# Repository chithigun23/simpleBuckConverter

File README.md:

# simpleBuckConverter

The aim is to create a simple buck converter design that can be easily used in other projects. The rough guideline is 12V to 5V with 2A of peak load, but still efficient at minimal load.

I've added the following features:

* Low current efficiency with automatic PFM and PWM mode switching
* Reverse polarity protection, with low quiescent current draw
* Transient voltage suppression diodes on input

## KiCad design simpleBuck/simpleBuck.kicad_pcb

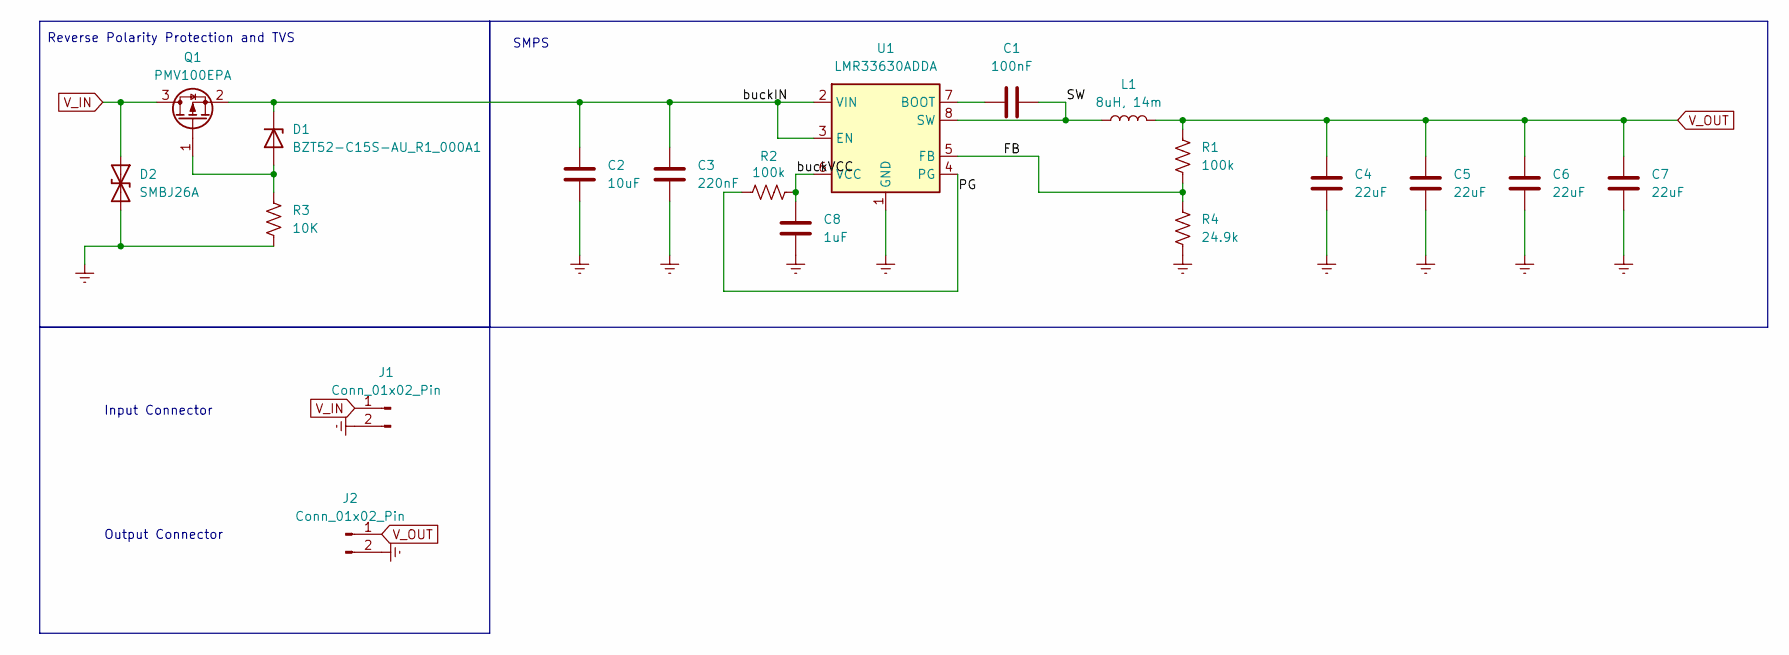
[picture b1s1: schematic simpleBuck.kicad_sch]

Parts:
C1: 100nF; C_0805_2012Metric_Pad1.18x1.45mm_HandSolder
C2: 10uF; C_0805_2012Metric_Pad1.18x1.45mm_HandSolder
C3: 220nF; C_0805_2012Metric_Pad1.18x1.45mm_HandSolder
C4, C5, C6, C7: 22uF; C_0805_2012Metric_Pad1.18x1.45mm_HandSolder
C8: 1uF; C_0805_2012Metric_Pad1.18x1.45mm_HandSolder
D1: BZT52-C15S-AU_R1_000A1; D_SOD-123
D2: SMBJ26A; C_0402_1005Metric_Pad0.74x0.62mm_HandSolder
J1, J2: Conn_01x02_Pin; PinHeader_1x02_P2.54mm_Vertical
L1: 8uH, 14m; L_TaiTech_TMPC1265_13.5x12.5mm
Q1: PMV100EPA; TSOT-23_HandSoldering
R1, R2: 100k; C_0805_2012Metric_Pad1.18x1.45mm_HandSolder
R3: 10K; C_0805_2012Metric_Pad1.18x1.45mm_HandSolder
R4: 24.9k; C_0805_2012Metric_Pad1.18x1.45mm_HandSolder
U1: LMR33630ADDA; Texas_HSOP-8-1EP_3.9x4.9mm_P1.27mm_ThermalVias

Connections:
/FB: R1.2, R4.1, U1.5 (FB)
/PG: R2.1, U1.4 (PG)
/SW: C1.2, L1.1, U1.8 (SW)
/buckIN: C2.1, C3.1, D1.1 (K), Q1.2 (S), U1.2 (VIN), U1.3 (EN)
/buckVCC: C8.1, R2.2, U1.6 (VCC)
GND: C2.2, C3.2, C4.2, C5.2, C6.2, C7.2, C8.2, D2.2 (A2), J1.2, J2.2, R3.2, R4.2, U1.1 (GND), U1.9 (GND)
unnamed: D1.2 (A), Q1.1 (G), R3.1
unnamed: C1.1, U1.7 (BOOT)
V_IN: D2.1 (A1), J1.1, Q1.3 (D)
V_OUT: C4.1, C5.1, C6.1, C7.1, J2.1, L1.2, R1.1

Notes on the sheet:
Reverse Polarity Protection and TVS
Output Connector
Input Connector
SMPS

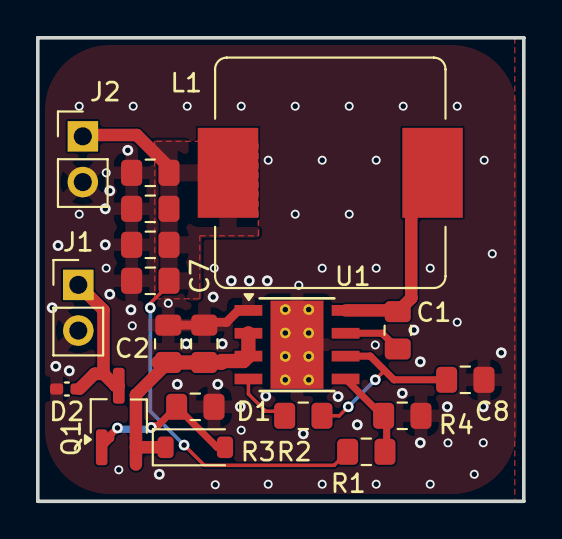
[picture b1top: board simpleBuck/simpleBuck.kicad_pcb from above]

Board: 2 copper layers, 27.0 x 25.8 mm, 19 parts (0 on the bottom side), 10 nets.

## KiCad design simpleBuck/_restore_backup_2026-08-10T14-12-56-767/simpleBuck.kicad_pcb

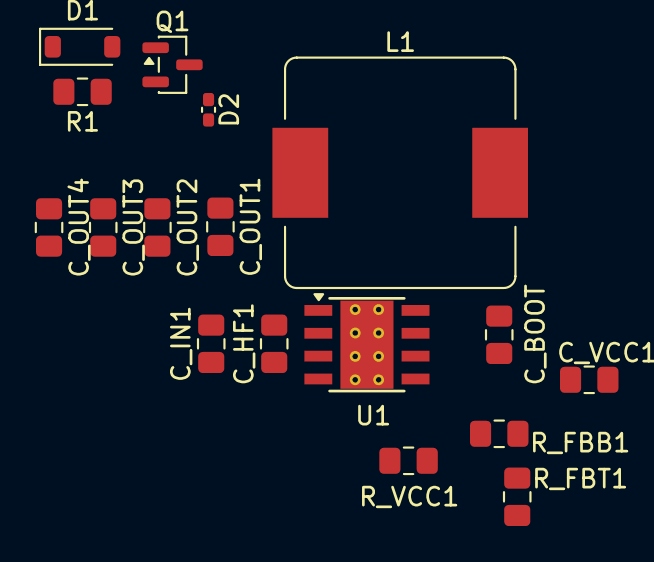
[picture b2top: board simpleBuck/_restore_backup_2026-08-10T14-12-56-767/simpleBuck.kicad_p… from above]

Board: 2 copper layers, 17 parts (0 on the bottom side), 10 nets, no tracks yet.

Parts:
C_BOOT: 100nF; C_0805_2012Metric_Pad1.18x1.45mm_HandSolder
C_HF1: 220nF; C_0805_2012Metric_Pad1.18x1.45mm_HandSolder
C_IN1: 10uF; C_0805_2012Metric_Pad1.18x1.45mm_HandSolder
C_OUT1, C_OUT2, C_OUT3, C_OUT4: 22uF; C_0805_2012Metric_Pad1.18x1.45mm_HandSolder
C_VCC1: 1uF; C_0805_2012Metric_Pad1.18x1.45mm_HandSolder
D1: BZT52-C15S-AU_R1_000A1; D_SOD-123
D2: D20V0L1B2LP-7B; C_0402_1005Metric_Pad0.74x0.62mm_HandSolder
L1: 8uH, 14m; L_TaiTech_TMPC1265_13.5x12.5mm
Q1: DMP3099LQ-7; SOT-23
R1: 10K; C_0805_2012Metric_Pad1.18x1.45mm_HandSolder
R_FBB1: 24.9k; C_0805_2012Metric_Pad1.18x1.45mm_HandSolder
R_FBT1: 100k; C_0805_2012Metric_Pad1.18x1.45mm_HandSolder
R_VCC1: 100k; C_0805_2012Metric_Pad1.18x1.45mm_HandSolder
U1: LMR33630ADDA; Texas_HSOP-8-1EP_3.9x4.9mm_P1.27mm_ThermalVias

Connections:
GND: C_HF1.2, C_IN1.2, C_OUT1.2, C_OUT2.2, C_OUT3.2, C_OUT4.2, C_VCC1.2, D2.2 (A2), R1.2, R_FBB1.2, U1.1 (GND), U1.9 (GND)
unnamed: D1.2 (A), Q1.1 (G), R1.1
unnamed: C_HF1.1, C_IN1.1, D1.1 (K), Q1.2 (S), U1.2 (VIN), U1.3 (EN)
unnamed: C_BOOT.1, U1.7 (BOOT)
unnamed: R_FBB1.1, R_FBT1.2, U1.5 (FB)
unnamed: R_VCC1.1, U1.4 (PG)
unnamed: C_BOOT.2, L1.1, U1.8 (SW)
unnamed: C_VCC1.1, R_VCC1.2, U1.6 (VCC)
V_IN: D2.1 (A1), Q1.3 (D)
V_OUT: C_OUT1.1, C_OUT2.1, C_OUT3.1, C_OUT4.1, L1.2, R_FBT1.1
